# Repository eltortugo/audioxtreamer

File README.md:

# AudioXtreamer
A simple multichannel USB/FPGA PCM audio interface:

Initially started as a simple way to add usb connectivity to the Yamaha 01x firewire based digital mixer & control surface, this project attempts to provide a simple low latency ASIO interface to a usb connected fpga that handles the i2s I/O.

Inspired by [Koon](https://sites.google.com/site/koonaudioprojects/usb-to-multi-channel-usb2-0) and his 24ch out usb interface, it builds further by providing 32in/32out on a simple usb2.0 interface and bypassing any vendor specific driver to communicate with the lowest possible latency with the fpga.

The proof of concept was built and written around the ft232h usb fifo in combination with a zynq fpga but it rapidly became clear that from a practical point of view, a more flexible Cypress FX2LP and a Xilinx Spartan 6 would suffice the needs of the interface. Although the code is now fully adapted to the 16bit data bus of the Cypress and the CoreGenerator fifos of ISE, it is easily portable to the original 8 bit FTDI and the new Vivado IP generator.

The AudioXtreamer can be seen as 3 different parts:
  - A generic C++ ASIO (TortugASIO) multi-threaded 32/64 bit driver that bridges the audio client/DAW to the USB backend
  - AudioXtreamer is a simple user mode driver that uses isochronous transfers to communicate with the fx2lp, plus a tray UI to          configure asio buffer sizes, channel count and midi ports. It uses USBDk/WinUSB as backend layer to the FX2LP.
  - VHDL fpga code for the Spartan 6 which handles the usb fifos, sample buffer and generation and decoding of the PCM I/O
  
The sources are written in such a way that the user can configure how many inputs and outputs can be handled in software and hardware.
 
To build the whole project you will need basic knowledge of C/C++ and Visual Studio, VHDL and ISE plus basic digital electronics skills.
 
The hardware implementation is based on the [ZTEX 2.01](https://www.ztex.de/usb-fpga-2/usb-fpga-2.01.e.html) but simple Aliexpress fx2lp / spartan6 parts should also work with minimal effort.

Xtreamer and ZTEX module for 01x |  PCB
:-------------------------:|:-------------------------:
  | 
  
  <p align="center">
  Yamaha 01x retrofitted with AudioXtreamer (USB/ADAT)

</p>

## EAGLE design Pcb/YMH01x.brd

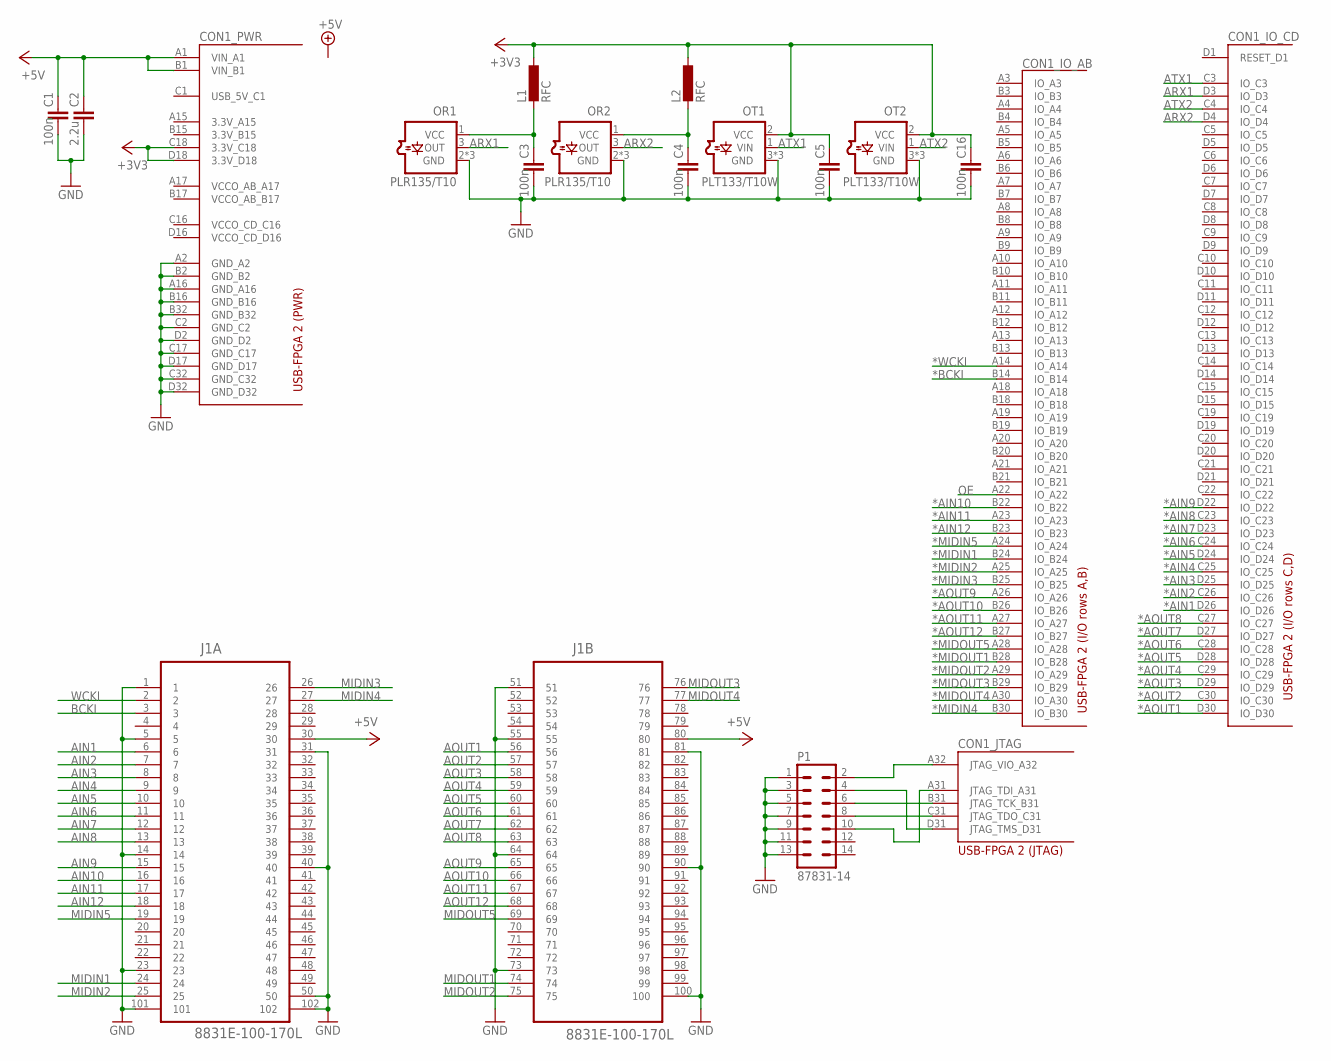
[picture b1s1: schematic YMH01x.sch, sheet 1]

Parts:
C1, C3, C4, C5, C16: 100n; C0603
C2: 2.2u; C0603
CON1: USB-FPGA-2THT; USB-FPGA-2-THT
J1: 8831E-100-170L; KEL_8831E-100-170L
L1, L2: RFC; L2012C
OR1, OR2: PLR135/T10
OT1, OT2: PLT133/T10W; PLT133/T10
P1: 87831-14

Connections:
*AIN1: CON1.D26 (IO_D26); also elsewhere on the board
*AIN2: CON1.C26 (IO_C26); also elsewhere on the board
*AIN3: CON1.D25 (IO_D25); also elsewhere on the board
*AIN4: CON1.C25 (IO_C25); also elsewhere on the board
*AIN5: CON1.D24 (IO_D24); also elsewhere on the board
*AIN6: CON1.C24 (IO_C24); also elsewhere on the board
*AIN7: CON1.D23 (IO_D23); also elsewhere on the board
*AIN8: CON1.C23 (IO_C23); also elsewhere on the board
*AIN9: CON1.D22 (IO_D22); also elsewhere on the board
*AIN10: CON1.B22 (IO_B22); also elsewhere on the board
*AIN11: CON1.A23 (IO_A23); also elsewhere on the board
*AIN12: CON1.B23 (IO_B23); also elsewhere on the board
*AOUT1: CON1.D30 (IO_D30); also elsewhere on the board
*AOUT2: CON1.C30 (IO_C30); also elsewhere on the board
*AOUT3: CON1.D29 (IO_D29); also elsewhere on the board
*AOUT4: CON1.C29 (IO_C29); also elsewhere on the board
*AOUT5: CON1.D28 (IO_D28); also elsewhere on the board
*AOUT6: CON1.C28 (IO_C28); also elsewhere on the board
*AOUT7: CON1.D27 (IO_D27); also elsewhere on the board
*AOUT8: CON1.C27 (IO_C27); also elsewhere on the board
*AOUT9: CON1.A26 (IO_A26); also elsewhere on the board
*AOUT10: CON1.B26 (IO_B26); also elsewhere on the board
*AOUT11: CON1.A27 (IO_A27); also elsewhere on the board
*AOUT12: CON1.B27 (IO_B27); also elsewhere on the board
*BCKI: CON1.B14 (IO_B14); also elsewhere on the board
*MIDIN1: CON1.B24 (IO_B24); also elsewhere on the board
*MIDIN2: CON1.A25 (IO_A25); also elsewhere on the board
*MIDIN3: CON1.B25 (IO_B25); also elsewhere on the board
*MIDIN4: CON1.B30 (IO_B30); also elsewhere on the board
*MIDIN5: CON1.A24 (IO_A24); also elsewhere on the board
*MIDOUT1: CON1.B28 (IO_B28); also elsewhere on the board
*MIDOUT2: CON1.A29 (IO_A29); also elsewhere on the board
*MIDOUT3: CON1.B29 (IO_B29); also elsewhere on the board
*MIDOUT4: CON1.A30 (IO_A30); also elsewhere on the board
*MIDOUT5: CON1.A28 (IO_A28); also elsewhere on the board
*WCKI: CON1.A14 (IO_A14); also elsewhere on the board
+3V3: C5.1, C16.1, CON1.C18 (3.3V_C18), CON1.D18 (3.3V_D18), L1.1, L2.1, OT1.2 (VCC), OT2.2 (VCC); also elsewhere on the board
+5V: C1.1, C2.1, CON1.A1 (VIN_A1), CON1.B1 (VIN_B1), J1.30, J1.80; also elsewhere on the board
AIN1: J1.6; also elsewhere on the board
AIN2: J1.7; also elsewhere on the board
AIN3: J1.8; also elsewhere on the board
AIN4: J1.9; also elsewhere on the board
AIN5: J1.10; also elsewhere on the board
AIN6: J1.11; also elsewhere on the board
AIN7: J1.12; also elsewhere on the board
AIN8: J1.13; also elsewhere on the board
AIN9: J1.15; also elsewhere on the board
AIN10: J1.16; also elsewhere on the board
AIN11: J1.17; also elsewhere on the board
AIN12: J1.18; also elsewhere on the board
AOUT1: J1.56; also elsewhere on the board
AOUT2: J1.57; also elsewhere on the board
AOUT3: J1.58; also elsewhere on the board
AOUT4: J1.59; also elsewhere on the board
AOUT5: J1.60; also elsewhere on the board
AOUT6: J1.61; also elsewhere on the board
AOUT7: J1.62; also elsewhere on the board
AOUT8: J1.63; also elsewhere on the board
AOUT9: J1.65; also elsewhere on the board
AOUT10: J1.66; also elsewhere on the board
AOUT11: J1.67; also elsewhere on the board
AOUT12: J1.68; also elsewhere on the board
ARX1: CON1.D3 (IO_D3), OR1.3 (OUT)
ARX2: CON1.D4 (IO_D4), OR2.3 (OUT)
ATX1: CON1.C3 (IO_C3), OT1.1 (VIN)
ATX2: CON1.C4 (IO_C4), OT2.1 (VIN)
BCKI: J1.3; also elsewhere on the board
GND: C1.2, C2.2, C3.2, C4.2, C5.2, C16.2, CON1.A2 (GND_A2), CON1.A16 (GND_A16), CON1.B2 (GND_B2), CON1.B16 (GND_B16), CON1.B32 (GND_B32), CON1.C2 (GND_C2), CON1.C17 (GND_C17), CON1.C32 (GND_C32), CON1.D2 (GND_D2), CON1.D17 (GND_D17), CON1.D32 (GND_D32), J1.1, J1.5, J1.14, J1.23, J1.31, J1.40, J1.50, J1.51, J1.55, J1.64, J1.73, J1.81, J1.90, J1.100, J1.101, J1.102, OR1.2 (GND), OR1.NC1 (GND), OR1.NC2 (GND), OR2.2 (GND), OR2.NC1 (GND), OR2.NC2 (GND), OT1.3 (GND), OT1.NC1 (GND), OT1.NC2 (GND), OT2.3 (GND), OT2.NC1 (GND), OT2.NC2 (GND), P1.1, P1.3, P1.5, P1.7, P1.9, P1.11, P1.13; also elsewhere on the board
MIDIN1: J1.24; also elsewhere on the board
MIDIN2: J1.25; also elsewhere on the board
MIDIN3: J1.26; also elsewhere on the board
MIDIN4: J1.27; also elsewhere on the board
MIDIN5: J1.19; also elsewhere on the board
MIDOUT1: J1.74; also elsewhere on the board
MIDOUT2: J1.75; also elsewhere on the board
MIDOUT3: J1.76; also elsewhere on the board
MIDOUT4: J1.77; also elsewhere on the board
MIDOUT5: J1.69; also elsewhere on the board
unnamed: CON1.A32 (JTAG_VIO_A32), P1.2
unnamed: CON1.D31 (JTAG_TMS_D31), P1.4
unnamed: CON1.B31 (JTAG_TCK_B31), P1.6
unnamed: CON1.C31 (JTAG_TDO_C31), P1.8
unnamed: CON1.A31 (JTAG_TDI_A31), P1.10
unnamed: C3.1, L1.2, OR1.1 (VCC)
unnamed: C4.1, L2.2, OR2.1 (VCC)
OE: CON1.A22 (IO_A22); also elsewhere on the board
WCKI: J1.2; also elsewhere on the board

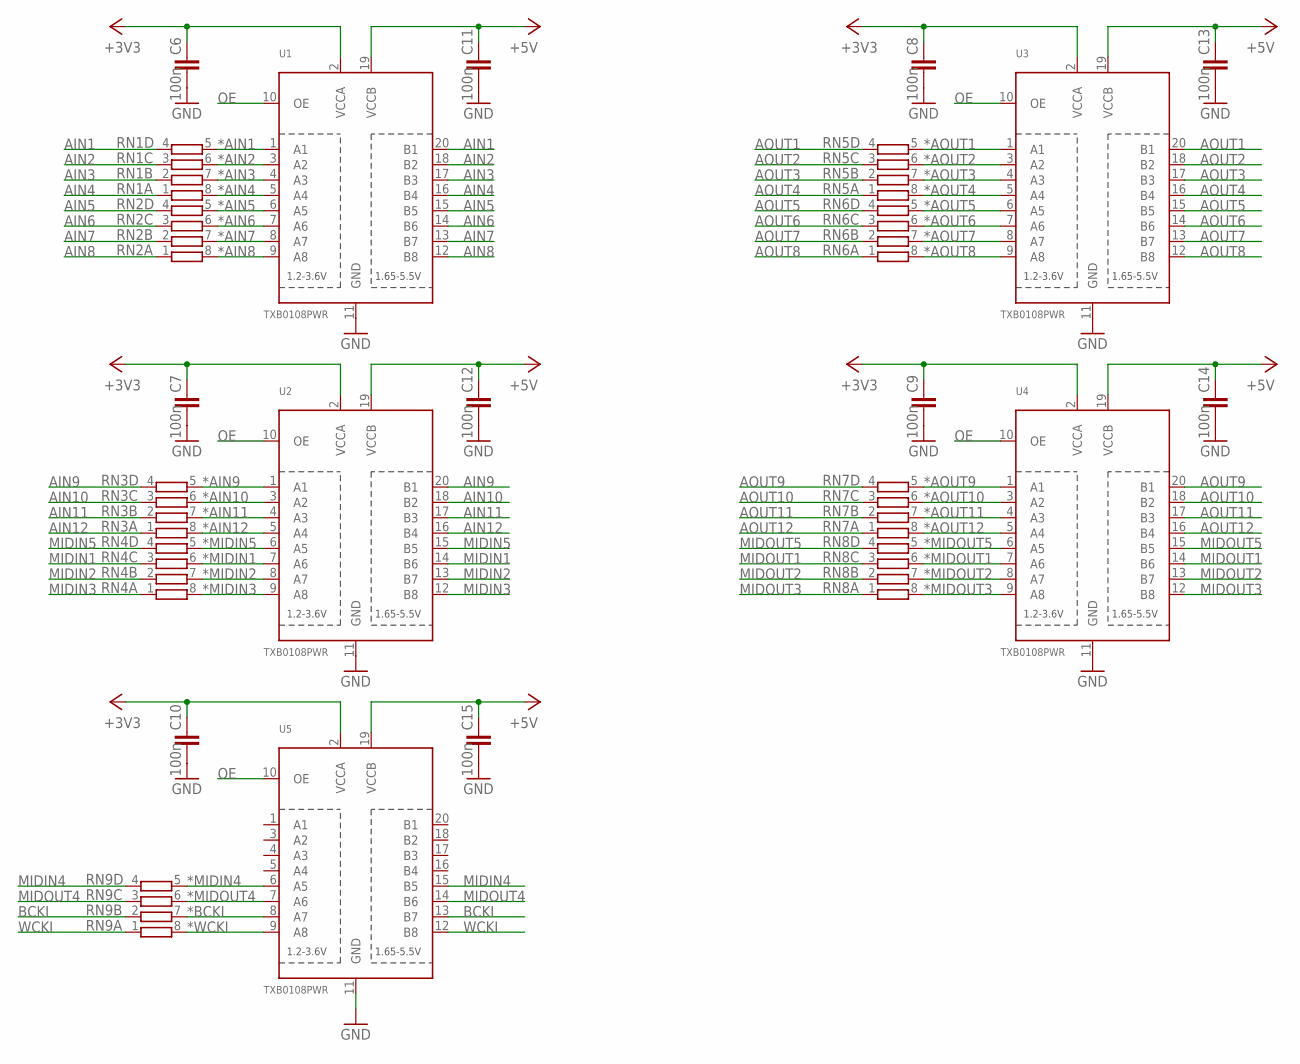
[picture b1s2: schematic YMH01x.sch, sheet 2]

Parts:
C6, C7, C8, C9, C10, C11, C12, C13, C14, C15: 100n; C0603
RN1, RN2, RN3, RN4, RN5, RN6, RN7, RN8, RN9: 4R-N0603-ARC; 0603-ARC
U1, U2, U3, U4, U5: TXB0108PWR; TSSOP20

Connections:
*AIN1: RN1.5 (2), U1.1 (A1); also elsewhere on the board
*AIN2: RN1.6 (2), U1.3 (A2); also elsewhere on the board
*AIN3: RN1.7 (2), U1.4 (A3); also elsewhere on the board
*AIN4: RN1.8 (2), U1.5 (A4); also elsewhere on the board
*AIN5: RN2.5 (2), U1.6 (A5); also elsewhere on the board
*AIN6: RN2.6 (2), U1.7 (A6); also elsewhere on the board
*AIN7: RN2.7 (2), U1.8 (A7); also elsewhere on the board
*AIN8: RN2.8 (2), U1.9 (A8); also elsewhere on the board
*AIN9: RN3.5 (2), U2.1 (A1); also elsewhere on the board
*AIN10: RN3.6 (2), U2.3 (A2); also elsewhere on the board
*AIN11: RN3.7 (2), U2.4 (A3); also elsewhere on the board
*AIN12: RN3.8 (2), U2.5 (A4); also elsewhere on the board
*AOUT1: RN5.5 (2), U3.1 (A1); also elsewhere on the board
*AOUT2: RN5.6 (2), U3.3 (A2); also elsewhere on the board
*AOUT3: RN5.7 (2), U3.4 (A3); also elsewhere on the board
*AOUT4: RN5.8 (2), U3.5 (A4); also elsewhere on the board
*AOUT5: RN6.5 (2), U3.6 (A5); also elsewhere on the board
*AOUT6: RN6.6 (2), U3.7 (A6); also elsewhere on the board
*AOUT7: RN6.7 (2), U3.8 (A7); also elsewhere on the board
*AOUT8: RN6.8 (2), U3.9 (A8); also elsewhere on the board
*AOUT9: RN7.5 (2), U4.1 (A1); also elsewhere on the board
*AOUT10: RN7.6 (2), U4.3 (A2); also elsewhere on the board
*AOUT11: RN7.7 (2), U4.4 (A3); also elsewhere on the board
*AOUT12: RN7.8 (2), U4.5 (A4); also elsewhere on the board
*BCKI: RN9.7 (2), U5.8 (A7); also elsewhere on the board
*MIDIN1: RN4.6 (2), U2.7 (A6); also elsewhere on the board
*MIDIN2: RN4.7 (2), U2.8 (A7); also elsewhere on the board
*MIDIN3: RN4.8 (2), U2.9 (A8); also elsewhere on the board
*MIDIN4: RN9.5 (2), U5.6 (A5); also elsewhere on the board
*MIDIN5: RN4.5 (2), U2.6 (A5); also elsewhere on the board
*MIDOUT1: RN8.6 (2), U4.7 (A6); also elsewhere on the board
*MIDOUT2: RN8.7 (2), U4.8 (A7); also elsewhere on the board
*MIDOUT3: RN8.8 (2), U4.9 (A8); also elsewhere on the board
*MIDOUT4: RN9.6 (2), U5.7 (A6); also elsewhere on the board
*MIDOUT5: RN8.5 (2), U4.6 (A5); also elsewhere on the board
*WCKI: RN9.8 (2), U5.9 (A8); also elsewhere on the board
+3V3: C6.1, C7.1, C8.1, C9.1, C10.1, U1.2 (VCCA), U2.2 (VCCA), U3.2 (VCCA), U4.2 (VCCA), U5.2 (VCCA); also elsewhere on the board
+5V: C11.1, C12.1, C13.1, C14.1, C15.1, U1.19 (VCCB), U2.19 (VCCB), U3.19 (VCCB), U4.19 (VCCB), U5.19 (VCCB); also elsewhere on the board
AIN1: RN1.4 (1), U1.20 (B1); also elsewhere on the board
AIN2: RN1.3 (1), U1.18 (B2); also elsewhere on the board
AIN3: RN1.2 (1), U1.17 (B3); also elsewhere on the board
AIN4: RN1.1, U1.16 (B4); also elsewhere on the board
AIN5: RN2.4 (1), U1.15 (B5); also elsewhere on the board
AIN6: RN2.3 (1), U1.14 (B6); also elsewhere on the board
AIN7: RN2.2 (1), U1.13 (B7); also elsewhere on the board
AIN8: RN2.1, U1.12 (B8); also elsewhere on the board
AIN9: RN3.4 (1), U2.20 (B1); also elsewhere on the board
AIN10: RN3.3 (1), U2.18 (B2); also elsewhere on the board
AIN11: RN3.2 (1), U2.17 (B3); also elsewhere on the board
AIN12: RN3.1, U2.16 (B4); also elsewhere on the board
AOUT1: RN5.4 (1), U3.20 (B1); also elsewhere on the board
AOUT2: RN5.3 (1), U3.18 (B2); also elsewhere on the board
AOUT3: RN5.2 (1), U3.17 (B3); also elsewhere on the board
AOUT4: RN5.1, U3.16 (B4); also elsewhere on the board
AOUT5: RN6.4 (1), U3.15 (B5); also elsewhere on the board
AOUT6: RN6.3 (1), U3.14 (B6); also elsewhere on the board
AOUT7: RN6.2 (1), U3.13 (B7); also elsewhere on the board
AOUT8: RN6.1, U3.12 (B8); also elsewhere on the board
AOUT9: RN7.4 (1), U4.20 (B1); also elsewhere on the board
AOUT10: RN7.3 (1), U4.18 (B2); also elsewhere on the board
AOUT11: RN7.2 (1), U4.17 (B3); also elsewhere on the board
AOUT12: RN7.1, U4.16 (B4); also elsewhere on the board
BCKI: RN9.2 (1), U5.13 (B7); also elsewhere on the board
GND: C6.2, C7.2, C8.2, C9.2, C10.2, C11.2, C12.2, C13.2, C14.2, C15.2, U1.11 (GND), U2.11 (GND), U3.11 (GND), U4.11 (GND), U5.11 (GND); also elsewhere on the board
MIDIN1: RN4.3 (1), U2.14 (B6); also elsewhere on the board
MIDIN2: RN4.2 (1), U2.13 (B7); also elsewhere on the board
MIDIN3: RN4.1, U2.12 (B8); also elsewhere on the board
MIDIN4: RN9.4 (1), U5.15 (B5); also elsewhere on the board
MIDIN5: RN4.4 (1), U2.15 (B5); also elsewhere on the board
MIDOUT1: RN8.3 (1), U4.14 (B6); also elsewhere on the board
MIDOUT2: RN8.2 (1), U4.13 (B7); also elsewhere on the board
MIDOUT3: RN8.1, U4.12 (B8); also elsewhere on the board
MIDOUT4: RN9.3 (1), U5.14 (B6); also elsewhere on the board
MIDOUT5: RN8.4 (1), U4.15 (B5); also elsewhere on the board
OE: U1.10 (OE), U2.10 (OE), U3.10 (OE), U4.10 (OE), U5.10 (OE); also elsewhere on the board
WCKI: RN9.1, U5.12 (B8); also elsewhere on the board

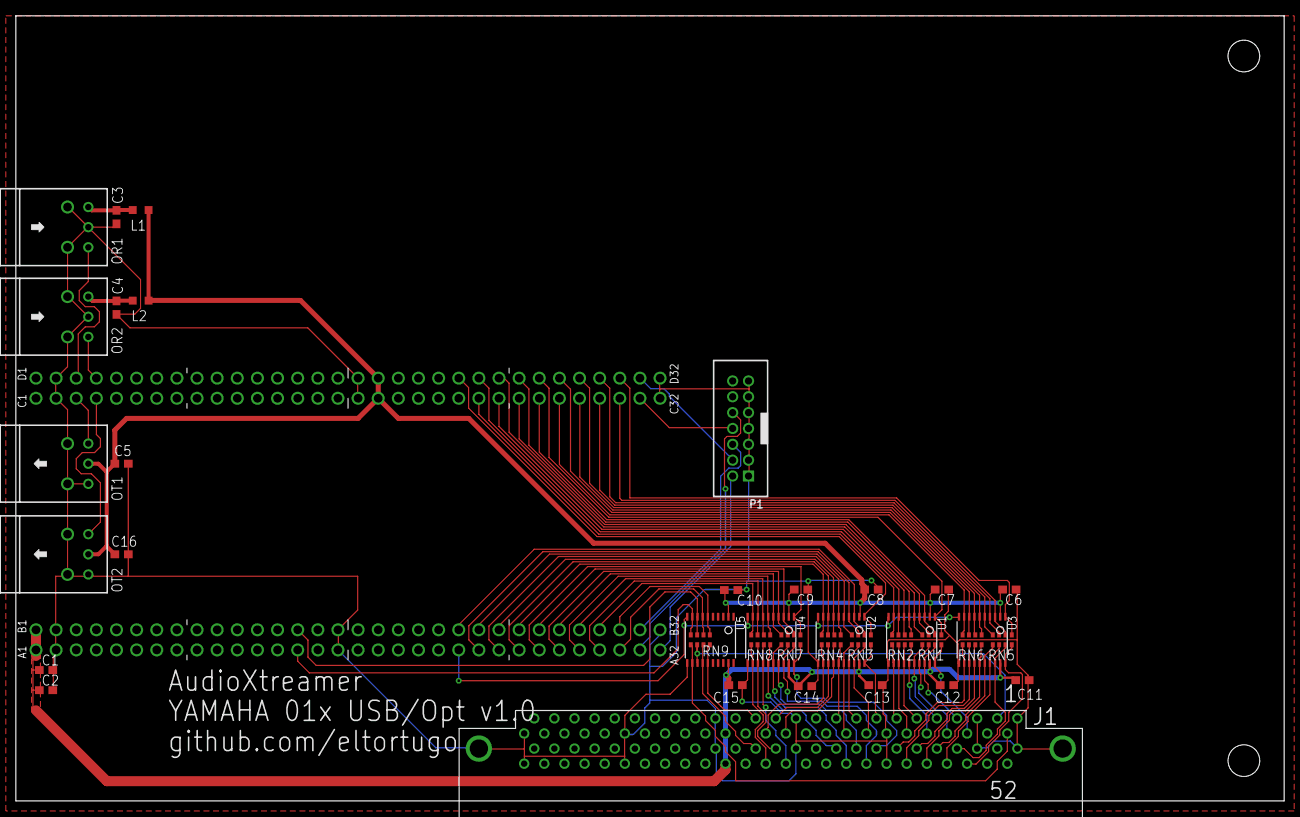
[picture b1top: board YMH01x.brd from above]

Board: 2 copper layers, 160.0 x 99.0 mm, 39 parts (0 on the bottom side), 87 nets.

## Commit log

2019-03-06 --eagle schematics and pcb layout files
2019-03-07 -Added Settings dialog to select the channel count and the buffer size -Added ini file initialize settings to configure the AudioXtreamer and the settings DialogProc -Added a small Tray Icon to start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
    -FPGA pinout constraints based on the AudioXtreamer pcb
    -Implementation of the lsi interface and simulation to configure the xtreamer core instead of through the audio packets
    -tons of refactor i
2019-03-23 AudioXtreamer: - this program is now the owner of the usb client and uses a memory mapped file to interchange the audio buffers with the asio driver. Named mutexes for synchronization. - There is now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
    TortugASIO:
    - All usb driver functionality moved out to AudioXtreamer and the asio driver now only communicates with it through memory mapped file, named mutexes and sendmessage
    - it is now possible to have a x64 dll to communicate with a x86 Xtreamer and viceversa.
2019-07-26 Isochronous IN /Bulk Out FIFO:(asynchronous audio)
    FIX: underrun at startup correct by precharging the output fifo
    FPGA: -output fifo cleanup and resize to 256 samples
    -coregen files versioned
    Xtreamer:
    -isoch xfers from 2 -> 4 , same for bulk out buffers, now with precharge
    -out fifo limited to 256 samples
2019-10-24 FEATURE: Full Iso in/out audio with MIDI
    CLEANUP: Main container rename
    ADDED: WinUSB/WinUSBHelper.cpp Backend
    CLEANUP: Move midi details to midi.cpp
    IMPROVEMENT: MMCSS priority time critical to worker thread
    ADDED: Schematics and Images
    FIX: Pipe abort after timeout solves lockup after usb cable disconnection/ hibernation
2019-12-26 Create LICENSE
2020-07-07 FEATURE: Wix installer. Company name and Copyright updated CLEANUP: some old defines. BUGFIX: using 16 uframes per xfer lead to empty fifo. Latencies can go down to 16 from now.
2020-07-07 FEATURE: usb midi out decoder and running status encoder + test bench CLEANUP: moved echol to sim pkg
2020-07-07 IMPROVEMENT: usbdk lib functions updated. Lib struct moved to cpp FEATURE: lsi replaced by new ex_lsi8 to increase the bandwidth and reduce latency for usb midi endpoint transfers in the fx2lp FEATUR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
2020-07-07 CLEANUP: software midi removed from project
2020-07-07 IMPROVEMENT: usb_midi_in and usb_midi_out tested in a chain for complete closed loop verification
2020-07-07 FEATURE: USB MIDI Class compliant CLEANUP: midi via isoch removed RENAME: isoch names introduced PROJECT: Files header decoration
2020-07-07 FEATURE: Asynchronous ep0 request of sample rate
2020-07-07 RENAME: top file and top instance now match
2020-07-07 FEATURE: FX2LP has now alternate settings for the interfaces to reserve isoch bandwidth only when active. IN_PROGRESS: preparations for isoch in/out active only when asio client is connected. BUGFIX: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
2020-07-07 IMPROVEMENT: Sample counter triggered now from the sof interrupt handler from the ezusb
2020-07-07 FEATURE: added support for 1024 samples ASIO buffer for compatibility with MixBUS BUILDFIX: installer relying on wrong arch file
2020-07-07 FEATURE: UAC 2.0 audio in and out, feedback endpoint data is being polled by the ezusb on ep6 in interrupt for now. : packet headers discarded for compatibility with uac2.0. eof marker introduced for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
2020-07-09 BUILDFIX: tortugasio dll uses now unicode version of combase
2020-07-23 REFACTOR: asio settings in ini file passing from AudioXtreamer to TortugASIO now beind done through shared memory. REFACTOR: renamed clock signals in top_audioxtreamer.vhd to correct simulation 1ps i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
2020-07-29 FEAT: usbdk updated to asynch ep0 requests / set alt ifc

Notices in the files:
parts and their libraries:
con-molex-milli-grid: Copyright (C) 2010, Bob Starr
